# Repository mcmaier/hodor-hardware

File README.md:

# HODOR - Highly flexible Open-source Door Operation Regulator

## Overview

HODOR ("Holds your door") is a universal controller for sliding door motor systems. The device is designed to operate brushed DC motors ranging from 12 to 24V, providing a comprehensive control solution that can be configured via Wi-Fi for smart home integration.

The hardware design files were created in KiCAD 9.0.

## System Architecture

The HODOR system consists of four main subsystems:

1. **Controllerboard** - Central processing unit based on the ESP32-S3
2. **Power Supply** - Handles voltage regulation and power distribution
3. **Motor Control** - Manages motor drive with H-bridge driver and feedback systems
4. **Peripherals** - Provides additional I/O and integration capabilities

### Block Diagram

```
+---------------+    +----------------+
|    Power      |    |                |
|   Terminals   |----| Controllerboard|
|   12-24V      |    |   (ESP32-S3)   |<--->[SPI BUS]
+---------------+    |                |
                     |                |----+
                     +----------------+    |
                            ^              |
                            |              v
                            |        +----------------+
                            |        |  Peripherals   |
                            |        +----------------+
                            v
                     +----------------+
                     |  Motor Control |
                     |   H-Bridge     |
                     |   Encoder I/F  |
                     +----------------+
```

## Technical Specifications

| Input Voltage | Standby Current |
|---------------|-----------------|
| 12 V          | tbc             |
| 24 V          | tbc             |

## Subsystems

### Controller Board (ESP32-S3)

The central controller is based on an ESP32-S3 microcontroller that handles:
- Motor control with PWM outputs
- Safety monitoring
- Encoder feedback processing
- SPI communication with peripherals
- Wi-Fi connectivity for configuration and smart home integration

The controller connects to both the motor control subsystem and peripheral I/O expansion modules through a combination of digital signals and an SPI bus.

### Power Supply

The power subsystem converts the 12-24V input to the required voltages for the control circuits and provides:
- Input voltage sensing (`V_BUS_SENSE`)
- DC-link voltage monitoring (`V_DC_SENSE`)
- Protection circuitry

### Motor Control

The motor control subsystem features:
- H-bridge driver with PWM inputs (`DRV_PWM1`, `DRV_PWM2`)
- Driver enable control (`DRV_EN`)
- Fault monitoring (`DRV_~SF`)
- Safety trigger and clear mechanisms (`SAFETY_TRIG`, `SAFETY_~CLR`)
- Current sensing (`ADC_I_SENSE`, `ADC_DRV_FB`)
- Quadrature encoder interface (`ENCODER_A`, `ENCODER_B`)
- An independet brake chopper, that burns voltage peaks above 27 V, to protect the driver IC.

The H-bridge allows bidirectional control of the DC motor with variable speed control via PWM.

### Peripherals

The control device provides:
- Inputs (Potential free or 12..24 V DC)
- Status indicators
- Relay output

## Key Features

- Supports brushed DC motors from 12 to 24V
- H-bridge driver with current sensing for motor protection
- Quadrature encoder interface for precise position feedback
- Configurable inputs
- Programmable relay output
- Wi-Fi connectivity for configuration and smart home integration
- Safety mechanisms for door operation
- Open-source hardware and software design

## Applications

The HODOR controller is primarily designed for:
- Sliding door automation
- Other motor control applications with optional position feedback

## Project Status

This project is currently in development.

## Safety Features

HODOR incorporates several safety features:
- Current monitoring to detect obstructions
- Position feedback via quadrature encoder
- Hardware watchdog safety trigger 
- Fault detection in the motor driver

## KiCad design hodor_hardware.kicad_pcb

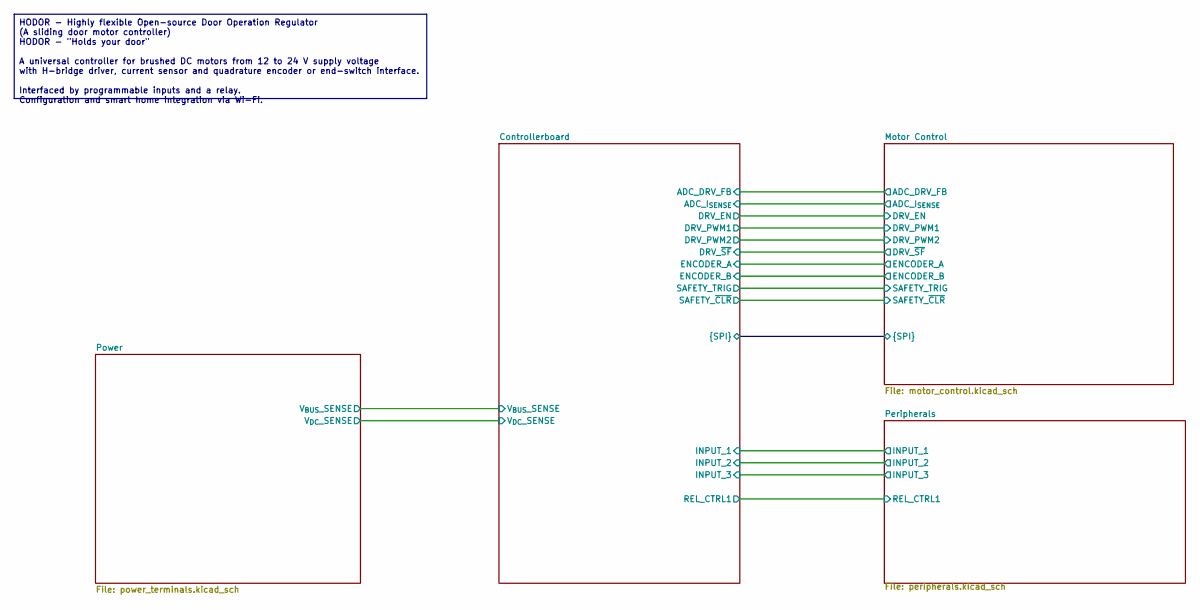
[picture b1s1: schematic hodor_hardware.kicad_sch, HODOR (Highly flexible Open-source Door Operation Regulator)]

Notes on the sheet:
HODOR - Highly flexible Open-source Door Operation Regulator (A sliding door motor controller) HODOR - "Holds your door" A universal controller for brushed DC motors from 12 to 24 V supply voltage with H-bridge driver, current sensor and quadrature encoder or end-switch interface. Interfaced by pro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

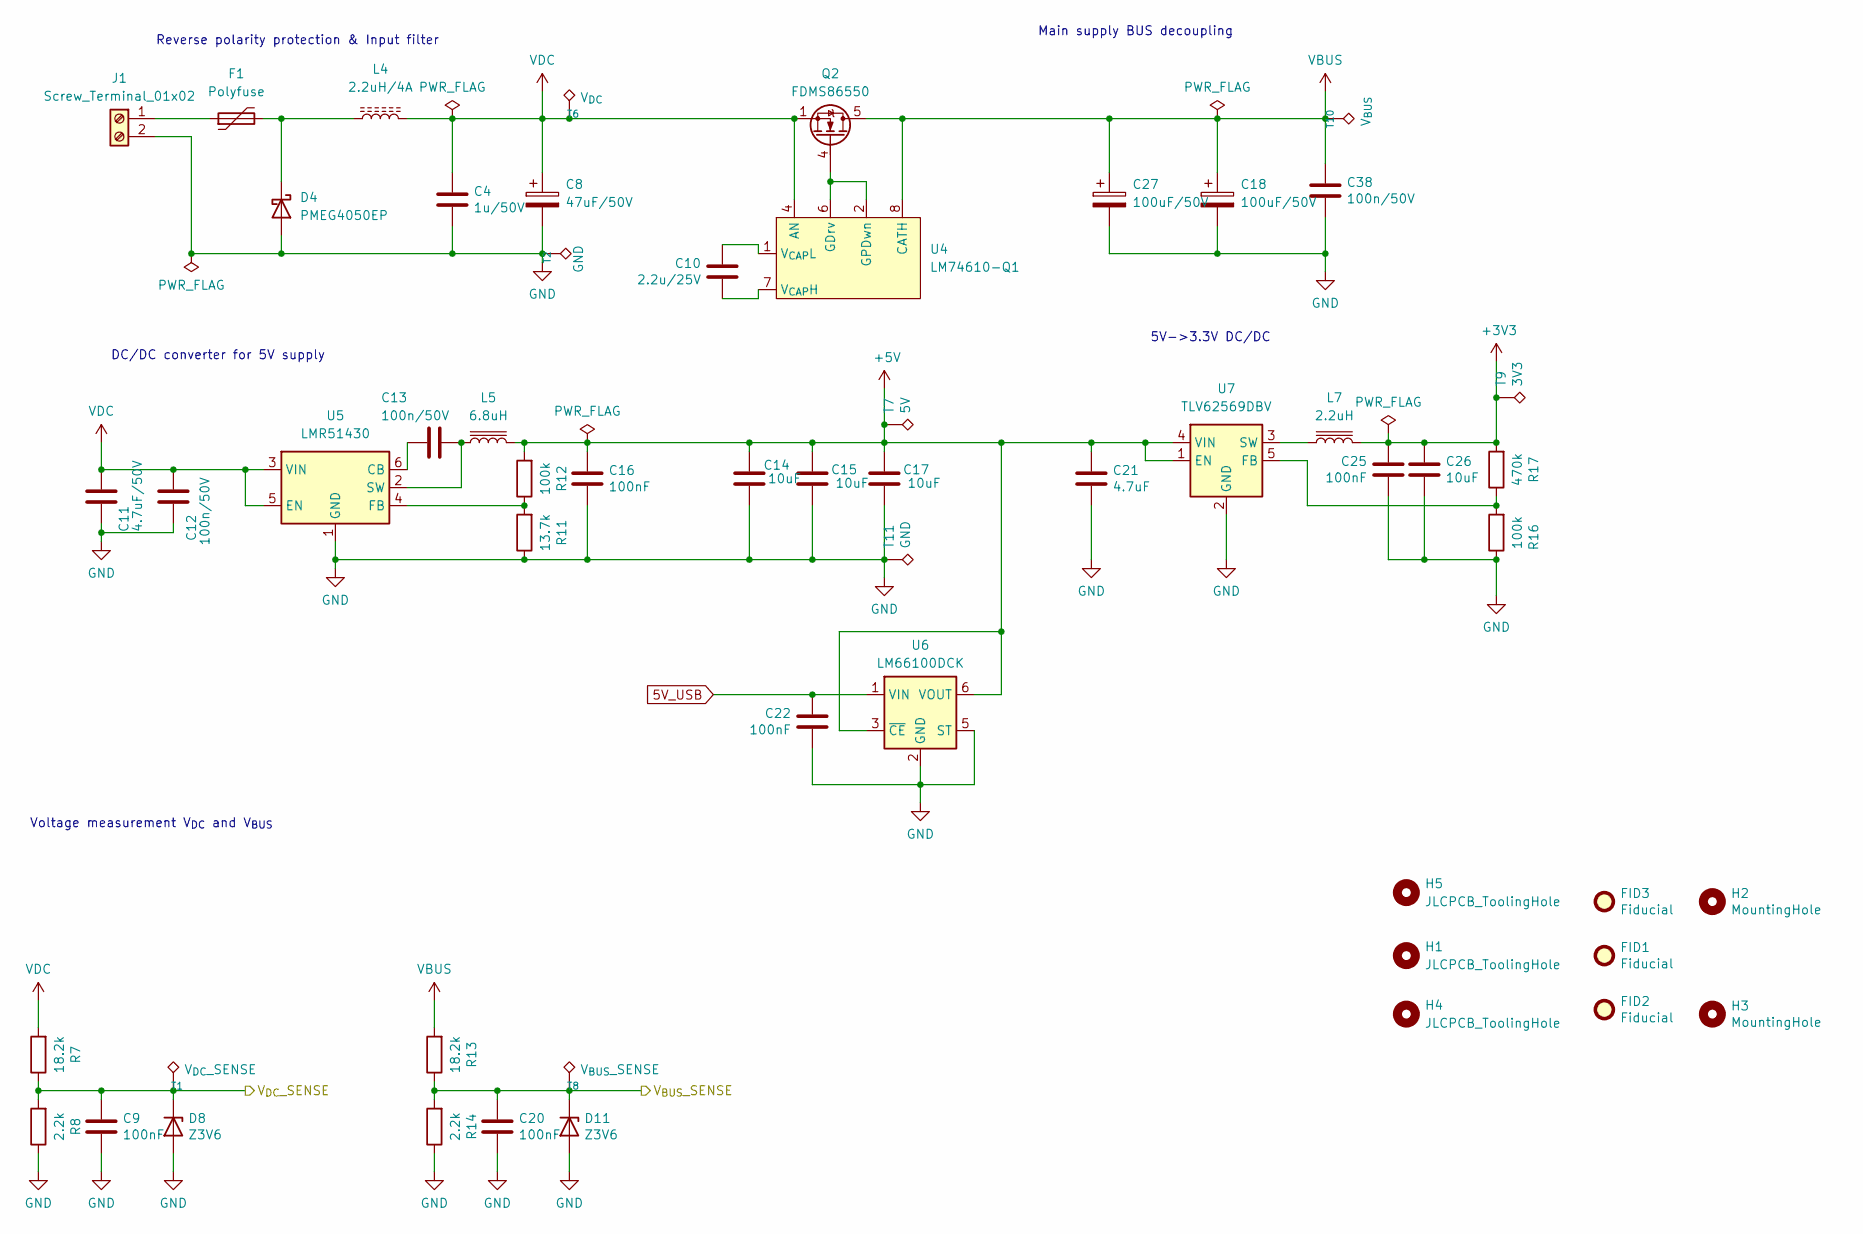
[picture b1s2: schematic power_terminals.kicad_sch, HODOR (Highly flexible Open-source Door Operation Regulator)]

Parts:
C4: 1u/50V; C_0805_2012Metric
C8: 47uF/50V; CP_Elec_6.3x5.8
C9, C16, C20, C22, C25: 100nF; C_0402_1005Metric
C10: 2.2u/25V; C_0805_2012Metric
C11: 4.7uF/50V; C_1206_3216Metric
C12, C13, C38: 100n/50V; C_0603_1608Metric
C14, C15, C17, C26: 10uF; C_0805_2012Metric
C18, C27: 100uF/50V; C_Elec_8x10.2
C21: 4.7uF; C_1206_3216Metric
D4: PMEG4050EP; D_SOD-128
D8, D11: Z3V6; D_SOD-523
F1: Polyfuse; Fuse_2920_7451Metric
FID1, FID2, FID3: Fiducial; Fiducial_1mm_Mask2mm
H1, H4, H5: JLCPCB_ToolingHole
H2, H3: MountingHole; MountingHole_3.2mm_M3
J1: Screw_Terminal_01x02; TerminalBlock_Phoenix_MKDS-1,5-2_1x02_P5.00mm_Horizontal
L4: 2.2uH/4A; L_Wuerth_MAPI-4020
L5: 6.8uH; L_Wuerth_WE-PD2-Typ-MS
L7: 2.2uH; L_1812_4532Metric
Q2: FDMS86550; TDSON-8-1
R7, R13: 18.2k; R_0402_1005Metric
R8, R14: 2.2k; R_0402_1005Metric
R11: 13.7k; R_0402_1005Metric
R12, R16: 100k; R_0402_1005Metric
R17: 470k; R_0402_1005Metric
T1: V_{DC}_SENSE; TestPoint_Pad_D1.0mm
T2, T11: GND; TestPoint_Pad_1.0x1.0mm
T6: V_{DC}; TestPoint_Pad_D1.0mm
T7: 5V; TestPoint_Pad_D1.0mm
T8: V_{BUS}_SENSE; TestPoint_Pad_D1.0mm
T9: 3V3; TestPoint_Pad_D1.0mm
T10: V_{BUS}; TestPoint_Pad_D1.0mm
U4: LM74610-Q1; VSSOP-8_3x3mm_P0.65mm
U5: LMR51430; SOT-23-6
U6: LM66100DCK; SOT-363_SC-70-6
U7: TLV62569DBV; SOT-23-5

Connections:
5V_USB: C22.2, U6.1 (VIN); also elsewhere on the board
+3V3: C25.1, C26.1, L7.2, R17.2, T9.1; also elsewhere on the board
+5V: C14.1, C15.1, C16.1, C17.1, C21.1, L5.2, R12.2, T7.1, U6.3 (~CE), U6.6 (VOUT), U7.1 (EN), U7.4 (VIN); also elsewhere on the board
/Controllerboard/V_{BUS}_SENSE: C20.1, D11.1 (K), R13.1, R14.2, T8.1; also elsewhere on the board
/Controllerboard/V_{DC}_SENSE: C9.1, D8.1 (K), R7.1, R8.2, T1.1; also elsewhere on the board
GND: C4.2, C8.2, C9.2, C11.2, C12.2, C14.2, C15.2, C16.2, C17.2, C18.2, C20.2, C21.2, C22.1, C25.2, C26.2, C27.2, C38.2, D4.2 (A), D8.2 (A), D11.2 (A), J1.2, R8.1, R11.1, R14.1, R16.1, T2.1, T11.1, U5.1 (GND), U6.2 (GND), U6.5 (ST), U7.2 (GND); also elsewhere on the board
unnamed: D4.1 (K), F1.2, L4.1
unnamed: F1.1, J1.1
unnamed: Q2.4 (G), U4.2 (GPDwn), U4.6 (GDrv)
unnamed: C10.2, U4.7 (V_{CAP}H)
unnamed: C10.1, U4.1 (V_{CAP}L)
unnamed: C13.2, U5.6 (CB)
unnamed: R11.2, R12.1, U5.4 (FB)
unnamed: C13.1, L5.1, U5.2 (SW)
unnamed: R16.2, R17.1, U7.5 (FB)
unnamed: L7.1, U7.3 (SW)
VBUS: C18.1, C27.1, C38.1, Q2.5 (D), R13.2, T10.1, U4.8 (CATH); also elsewhere on the board
VDC: C4.1, C8.1, C11.1, C12.1, L4.2, Q2.1 (S), Q2.2 (S), Q2.3 (S), R7.2, T6.1, U4.4 (AN), U5.3 (VIN), U5.5 (EN)

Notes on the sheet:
DC/DC converter for 5V supply
5V->3.3V DC/DC
Voltage measurement V_{DC} and V_{BUS}
Reverse polarity protection & Input filter
Main supply BUS decoupling

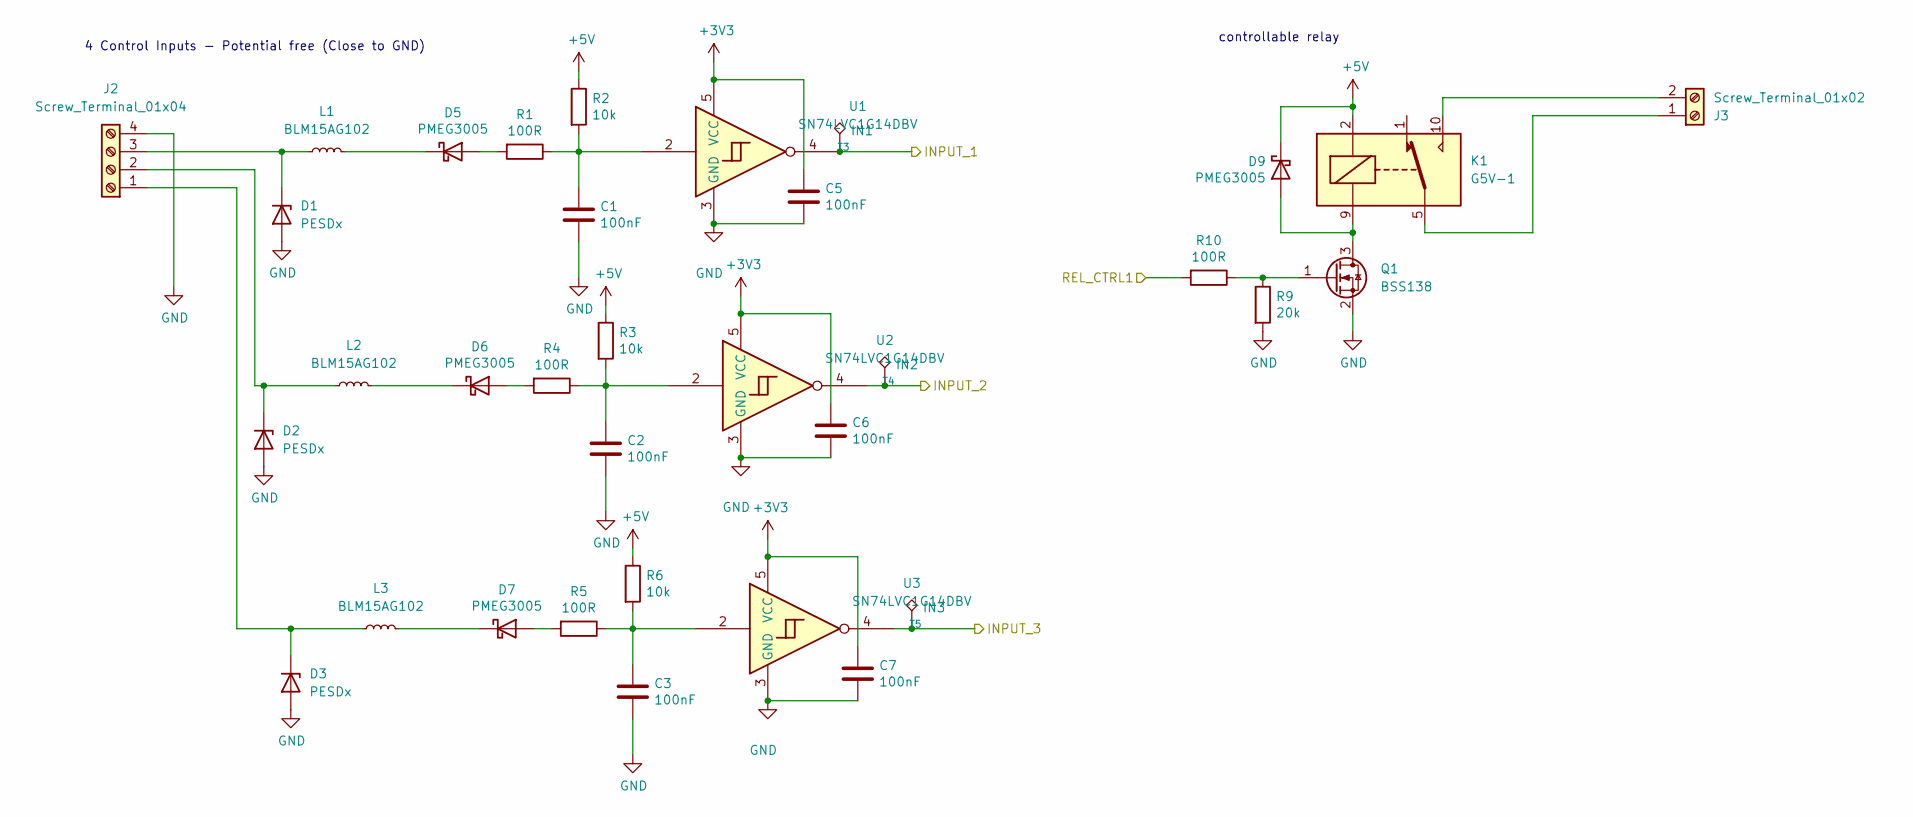
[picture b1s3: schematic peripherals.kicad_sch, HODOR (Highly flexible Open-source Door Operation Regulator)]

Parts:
C1, C2, C3, C5, C6, C7: 100nF; C_0402_1005Metric
D1, D2, D3: PESDx; D_SOD-523
D5, D6, D7, D9: PMEG3005; D_SOD-523
J2: Screw_Terminal_01x04; TerminalBlock_Phoenix_MKDS-1,5-4_1x04_P5.00mm_Horizontal
J3: Screw_Terminal_01x02; TerminalBlock_Phoenix_MKDS-1,5-2_1x02_P5.00mm_Horizontal
K1: G5V-1; Relay_SPDT_Omron_G5V-1
L1, L2, L3: BLM15AG102; L_0402_1005Metric
Q1: BSS138; SOT-23
R1, R4, R5, R10: 100R; R_0402_1005Metric
R2, R3, R6: 10k; R_0402_1005Metric
R9: 20k; R_0402_1005Metric
T3: IN1; TestPoint_Pad_D1.0mm
T4: IN2; TestPoint_Pad_D1.0mm
T5: IN3; TestPoint_Pad_D1.0mm
U1, U2, U3: SN74LVC1G14DBV; SOT-23-5

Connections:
+3V3: C5.1, C6.1, C7.1, U1.5 (VCC), U2.5 (VCC), U3.5 (VCC); also elsewhere on the board
+5V: D9.1 (K), K1.2, R2.1, R3.1, R6.1; also elsewhere on the board
/Controllerboard/INPUT_1: T3.1, U1.4; also elsewhere on the board
/Controllerboard/INPUT_2: T4.1, U2.4; also elsewhere on the board
/Controllerboard/INPUT_3: T5.1, U3.4; also elsewhere on the board
/Controllerboard/REL_CTRL1: R10.2; also elsewhere on the board
GND: C1.2, C2.2, C3.2, C5.2, C6.2, C7.2, D1.2 (A), D2.2 (A), D3.2 (A), J2.4, Q1.2 (S), R9.2, U1.3 (GND), U2.3 (GND), U3.3 (GND); also elsewhere on the board
unnamed: C1.1, R1.1, R2.2, U1.2
unnamed: C2.1, R3.2, R4.1, U2.2
unnamed: C3.1, R5.1, R6.2, U3.2
unnamed: D1.1 (K), J2.3, L1.1
unnamed: D2.1 (K), J2.2, L2.1
unnamed: D3.1 (K), J2.1, L3.1
unnamed: D5.2 (A), R1.2
unnamed: D5.1 (K), L1.2
unnamed: D6.2 (A), R4.2
unnamed: D6.1 (K), L2.2
unnamed: D7.2 (A), R5.2
unnamed: D7.1 (K), L3.2
unnamed: D9.2 (A), K1.9, Q1.3 (D)
unnamed: J3.1, K1.5, K1.6
unnamed: J3.2, K1.10
unnamed: Q1.1 (G), R9.1, R10.1

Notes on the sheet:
4 Control Inputs - Potential free (Close to GND)
controllable relay

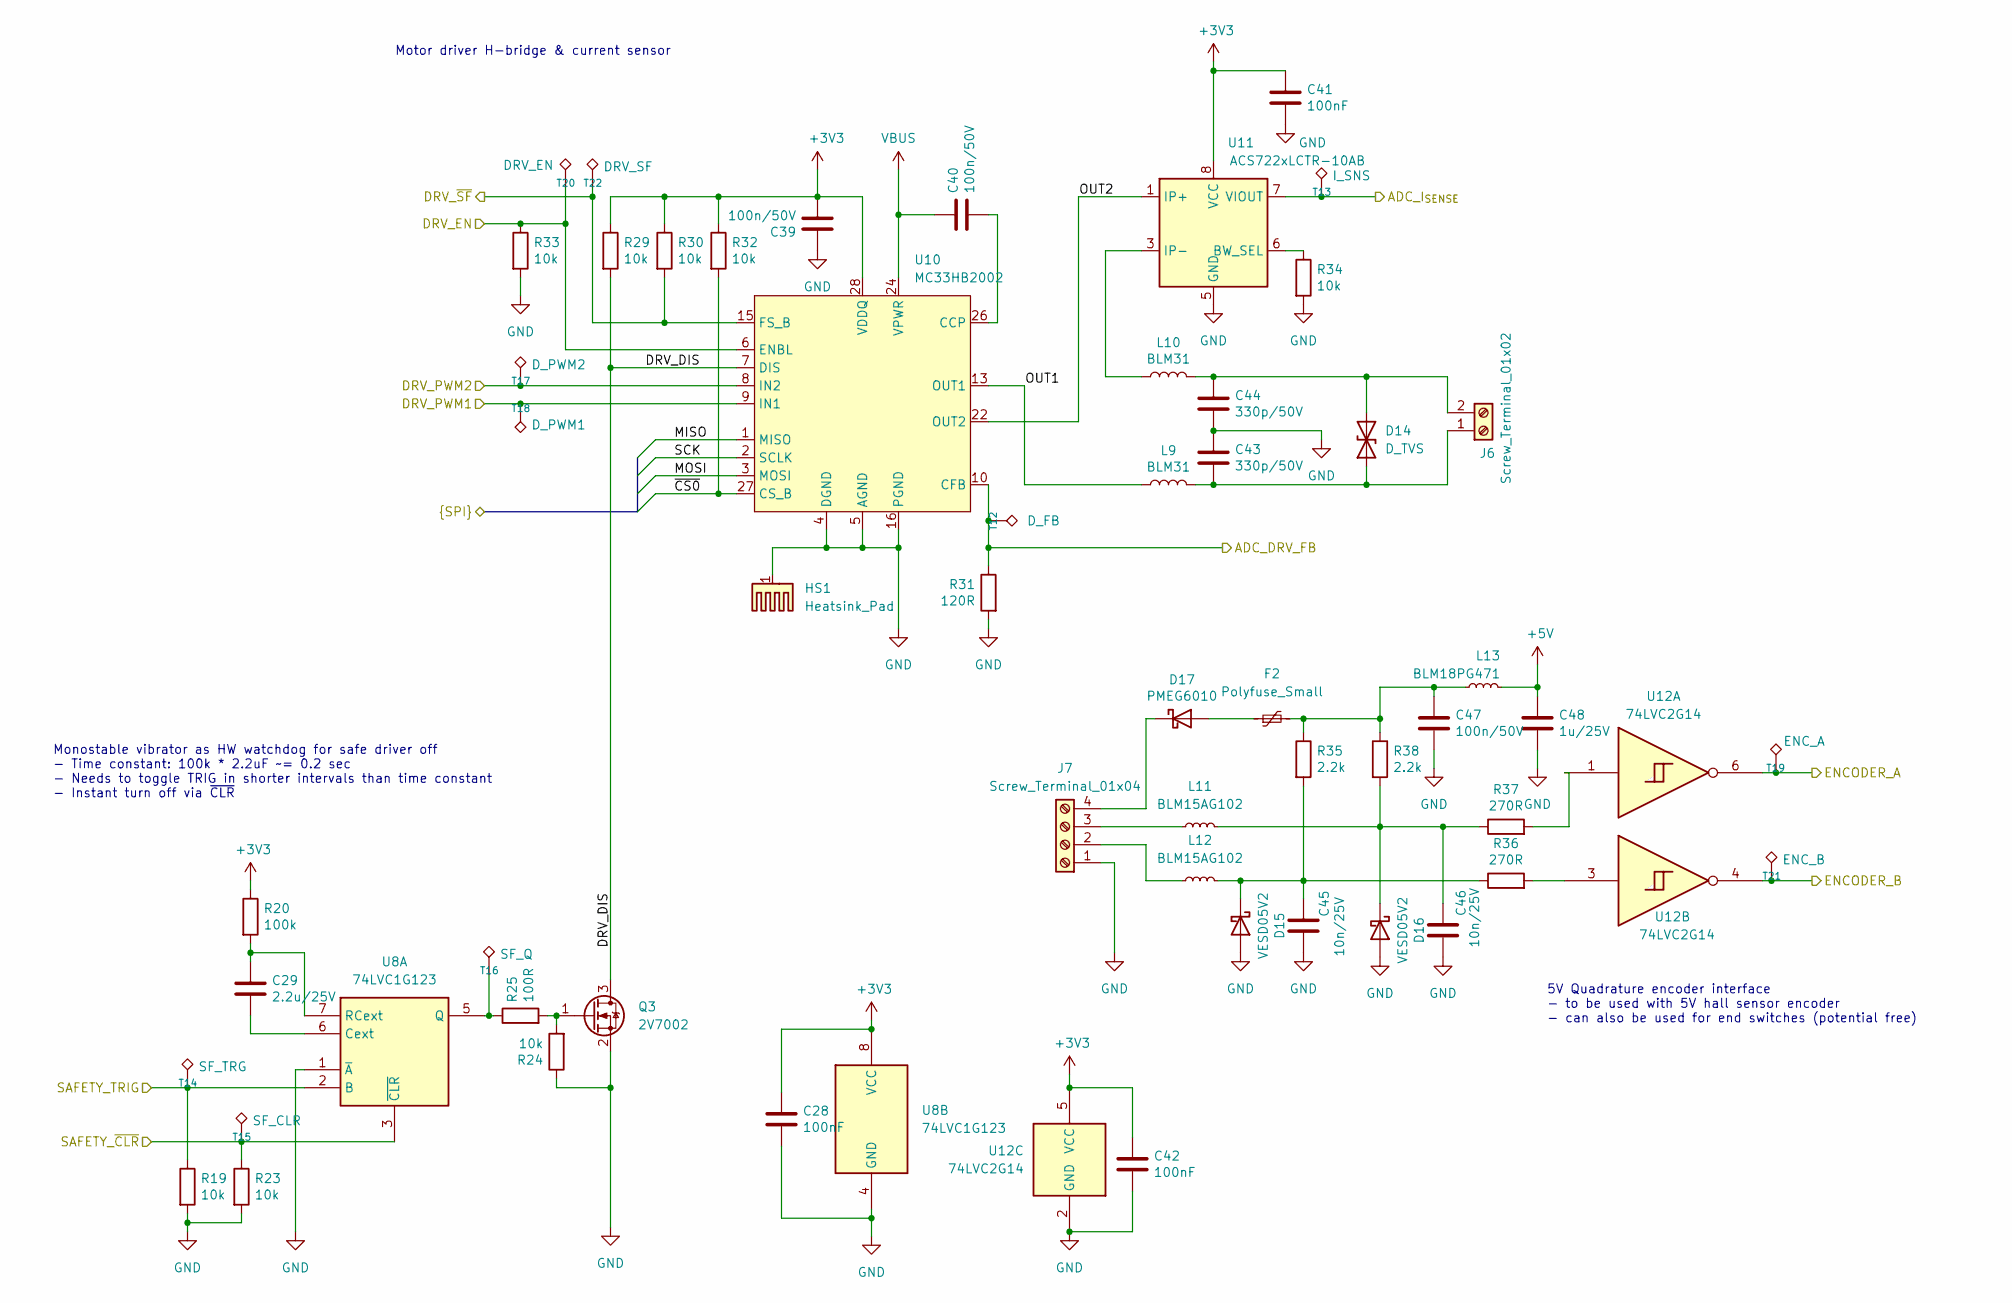
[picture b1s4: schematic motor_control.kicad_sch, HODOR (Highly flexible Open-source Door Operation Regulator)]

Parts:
C28, C41, C42: 100nF; C_0402_1005Metric
C29: 2.2u/25V; C_0805_2012Metric
C39, C40, C47: 100n/50V; C_0603_1608Metric
C43, C44: 330p/50V; C_0603_1608Metric
C45, C46: 10n/25V; C_0402_1005Metric
C48: 1u/25V; C_0603_1608Metric
D14: D_TVS; D_SMB
D15, D16: VESD05V2; D_SOD-523
D17: PMEG6010; D_SOD-123F
F2: Polyfuse_Small; Fuse_0805_2012Metric
HS1: Heatsink_Pad; Heatsink_AAVID_573300D00010G_TO-263
J6: Screw_Terminal_01x02; TerminalBlock_Phoenix_MKDS-1,5-2_1x02_P5.00mm_Horizontal
J7: Screw_Terminal_01x04; TerminalBlock_Phoenix_MKDS-1,5-4_1x04_P5.00mm_Horizontal
L9, L10: BLM31; L_1206_3216Metric
L11, L12: BLM15AG102; L_0402_1005Metric
L13: BLM18PG471; L_0603_1608Metric
Q3: 2V7002; SOT-323_SC-70
R19, R23, R24, R29, R30, R32, R33, R34: 10k; R_0402_1005Metric
R20: 100k; R_0402_1005Metric
R25: 100R; R_0402_1005Metric
R31: 120R; R_0603_1608Metric
R35, R38: 2.2k; R_0402_1005Metric
R36, R37: 270R; R_0402_1005Metric
T12: D_FB; TestPoint_Pad_D1.0mm
T13: I_SNS; TestPoint_Pad_D1.0mm
T14: SF_TRG; TestPoint_Pad_D1.0mm
T15: SF_CLR; TestPoint_Pad_D1.0mm
T16: SF_Q; TestPoint_Pad_D1.0mm
T17: D_PWM2; TestPoint_Pad_D1.0mm
T18: D_PWM1; TestPoint_Pad_D1.0mm
T19: ENC_A; TestPoint_Pad_D1.0mm
T20: DRV_EN; TestPoint_Pad_D1.0mm
T21: ENC_B; TestPoint_Pad_D1.0mm
T22: DRV_SF; TestPoint_Pad_D1.0mm
U8: 74LVC1G123; VSSOP-8_2.3x2mm_P0.5mm
U10: MC33HB2002; HVQFN-28-1EP_6x6mm_MC33HB2002
U11: ACS722xLCTR-10AB; SOIC-8_3.9x4.9mm_P1.27mm
U12: 74LVC2G14; SOT-23-6

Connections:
+3V3: C28.1, C39.2, C41.1, C42.1, R20.1, R29.1, R30.1, R32.1, U8.8 (VCC), U10.28 (VDDQ), U11.8 (VCC), U12.5 (VCC); also elsewhere on the board
+5V: C48.1, L13.2; also elsewhere on the board
/Controllerboard/ADC_DRV_FB: R31.1, T12.1, U10.10 (CFB); also elsewhere on the board
/Controllerboard/ADC_I_{SENSE}: T13.1, U11.7 (VIOUT); also elsewhere on the board
/Controllerboard/DRV_EN: R33.1, T20.1, U10.6 (ENBL); also elsewhere on the board
/Controllerboard/DRV_PWM1: T18.1, U10.9 (IN1); also elsewhere on the board
/Controllerboard/DRV_PWM2: T17.1, U10.8 (IN2); also elsewhere on the board
/Controllerboard/DRV_~SF: R30.2, T22.1, U10.15 (FS_B); also elsewhere on the board
/Controllerboard/ENCODER_A: T19.1, U12.6; also elsewhere on the board
/Controllerboard/ENCODER_B: T21.1, U12.4; also elsewhere on the board
/Controllerboard/MISO: U10.1 (MISO); also elsewhere on the board
/Controllerboard/MOSI: U10.3 (MOSI); also elsewhere on the board
/Controllerboard/SAFETY_TRIG: R19.1, T14.1, U8.2 (B); also elsewhere on the board
/Controllerboard/SAFETY_~CLR: R23.1, T15.1, U8.3 (~CLR); also elsewhere on the board
/Controllerboard/SCK: U10.2 (SCLK); also elsewhere on the board
/Controllerboard/~CS0: R32.2, U10.27 (CS_B); also elsewhere on the board
/Motor Control/DRV_DIS: Q3.3 (D), R29.2, U10.7 (DIS)
/Motor Control/OUT1: L9.1, U10.13 (OUT1), U10.14 (OUT1)
/Motor Control/OUT2: U10.22 (OUT2), U10.23 (OUT2), U11.1 (IP+), U11.2 (IP+)
GND: C28.2, C39.1, C41.2, C42.2, C43.1, C44.2, C45.2, C46.2, C47.2, C48.2, D15.2 (A), D16.2 (A), HS1.1, J7.1, Q3.2 (S), R19.2, R23.2, R24.1, R31.2, R33.2, R34.2, U8.1 (~A), U8.4 (GND), U10.4 (DGND), U10.5 (AGND), U10.16 (PGND), U10.17 (PGND), U10.18 (PGND), U10.19 (PGND), U10.20 (PGND), U10.21 (AGND), U10.29 (AGND), U11.5 (GND), U12.2 (GND); also elsewhere on the board
unnamed: C47.1, F2.2, L13.1, R35.1, R38.1
unnamed: C43.2, D14.1 (A1), J6.1, L9.2
unnamed: C44.1, D14.2 (A2), J6.2, L10.2
unnamed: C45.1, D15.1 (K), L12.2, R35.2, R36.1
unnamed: C46.1, D16.1 (K), L11.2, R37.1, R38.2
unnamed: D17.2 (A), F2.1
unnamed: D17.1 (K), J7.4
unnamed: J7.2, L12.1
unnamed: J7.3, L11.1
unnamed: L10.1, U11.3 (IP-), U11.4 (IP-)
unnamed: Q3.1 (G), R24.2, R25.2
unnamed: R36.2, U12.3
unnamed: R37.2, U12.1
unnamed: C29.2, U8.6 (Cext)
unnamed: R25.1, T16.1, U8.5 (Q)
unnamed: C29.1, R20.2, U8.7 (RCext)
unnamed: C40.2, U10.26 (CCP)
unnamed: R34.1, U11.6 (BW_SEL)
VBUS: C40.1, U10.11 (VPWR), U10.12 (VPWR), U10.24 (VPWR), U10.25 (VPWR); also elsewhere on the board

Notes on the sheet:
5V Quadrature encoder interface - to be used with 5V hall sensor encoder - can also be used for end switches (potential free)
Motor driver H-bridge & current sensor
Monostable vibrator as HW watchdog for safe driver off - Time constant: 100k * 2.2uF ~= 0.2 sec - Needs to toggle TRIG in shorter intervals than time constant - Instant turn off via ~{CLR}

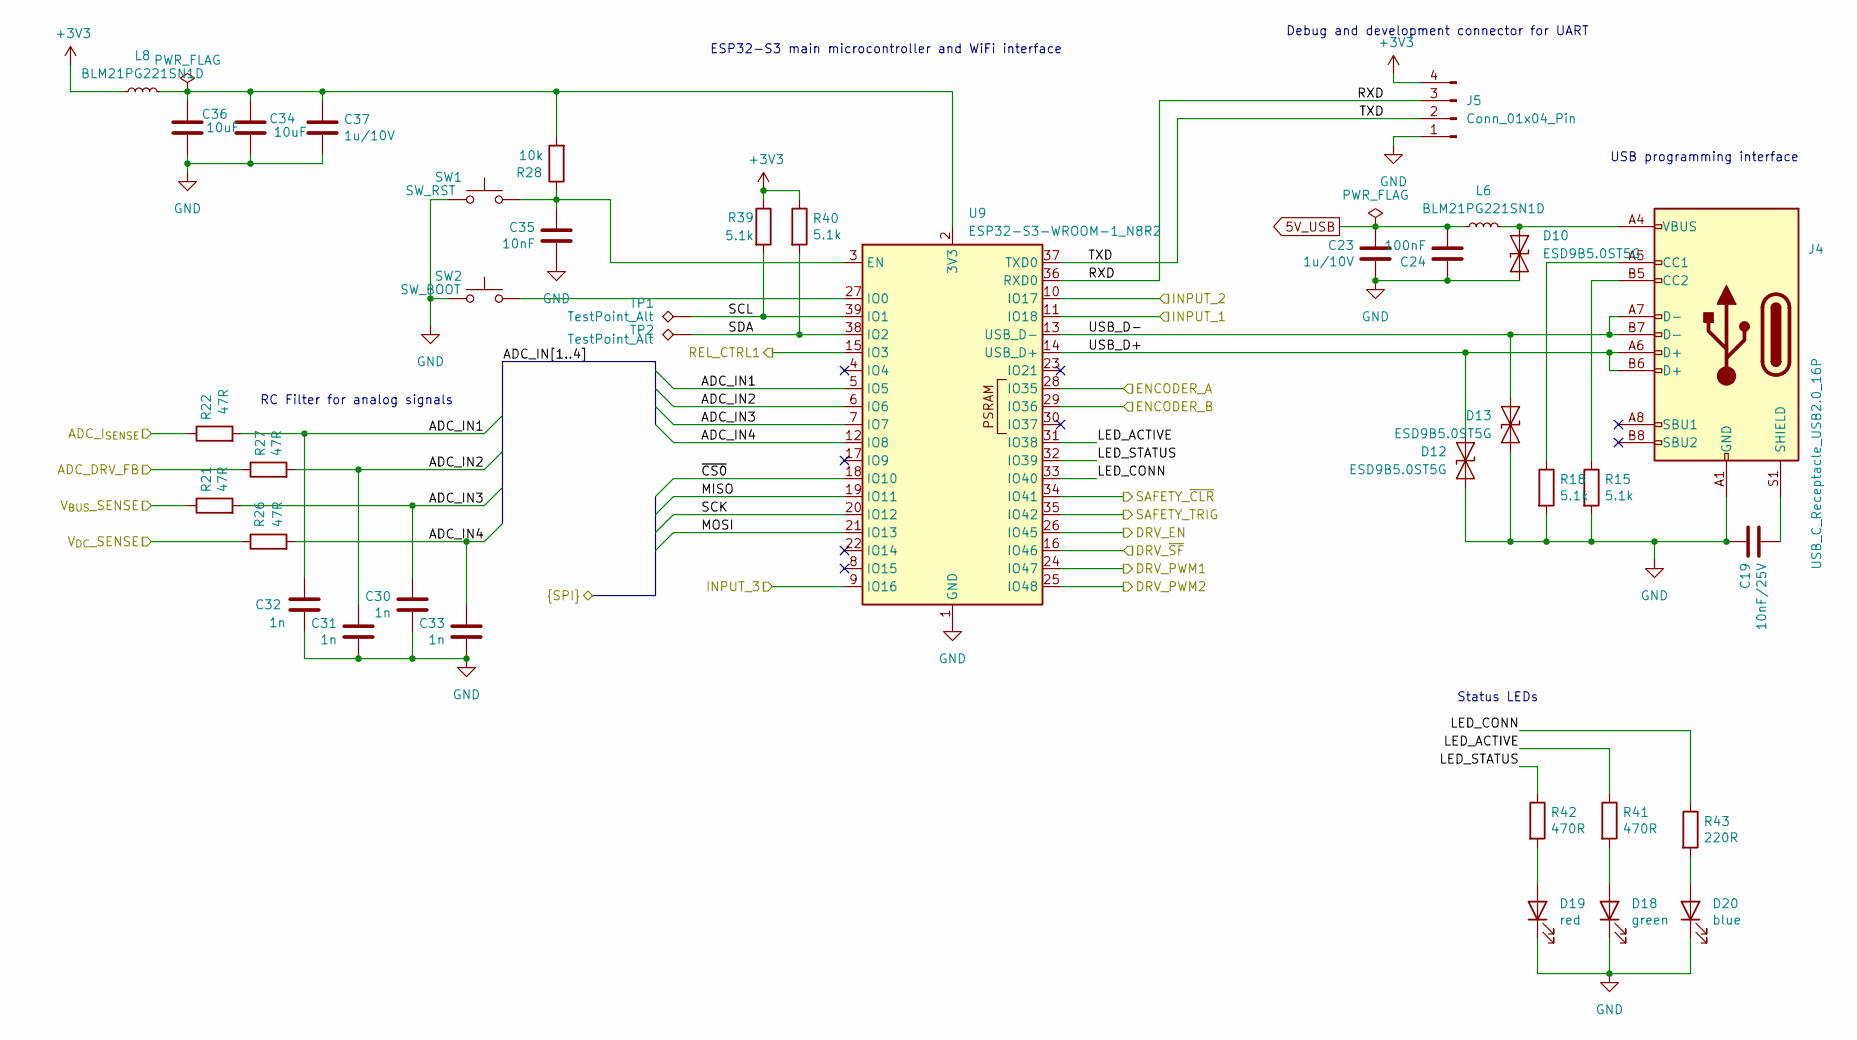
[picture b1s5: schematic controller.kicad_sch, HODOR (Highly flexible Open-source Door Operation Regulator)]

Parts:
C19: 10nF/25V; C_0402_1005Metric
C23, C37: 1u/10V; C_0402_1005Metric
C24: 100nF; C_0402_1005Metric
C30, C31, C32, C33: 1n; C_0402_1005Metric
C34, C36: 10uF; C_0805_2012Metric
C35: 10nF; C_0402_1005Metric
D10, D12, D13: ESD9B5.0ST5G; D_SOD-923
D18: green; LED_0603_1608Metric
D19: red; LED_0603_1608Metric
D20: blue; LED_0603_1608Metric
J4: USB_C_Receptacle_USB2.0_16P; USB_C_Receptacle_G-Switch_GT-USB-7010ASV
J5: Conn_01x04_Pin; PinHeader_1x04_P2.54mm_Vertical
L6, L8: BLM21PG221SN1D; L_0805_2012Metric
R15, R18, R39, R40: 5.1k; R_0402_1005Metric
R21, R22, R26, R27: 47R; R_0402_1005Metric
R28: 10k; R_0402_1005Metric
R41, R42: 470R; R_0402_1005Metric
R43: 220R; R_0402_1005Metric
SW1: SW_RST; SW_Push_SPST_NO_Alps_SKRK
SW2: SW_BOOT; SW_Push_SPST_NO_Alps_SKRK
TP1, TP2: TestPoint_Alt; TestPoint_Pad_1.0x1.0mm
U9: ESP32-S3-WROOM-1_N8R2; ESP32-S3-WROOM-1U

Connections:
5V_USB: C23.2, C24.1, L6.1; also elsewhere on the board
+3V3: J5.4, L8.1, R39.1, R40.1; also elsewhere on the board
/Controllerboard/ADC_DRV_FB: R27.1; also elsewhere on the board
/Controllerboard/ADC_IN1: C32.2, R22.2, U9.5 (IO5)
/Controllerboard/ADC_IN2: C31.2, R27.2, U9.6 (IO6)
/Controllerboard/ADC_IN3: C30.2, R21.2, U9.7 (IO7)
/Controllerboard/ADC_IN4: C33.2, R26.2, U9.12 (IO8)
/Controllerboard/ADC_I_{SENSE}: R22.1; also elsewhere on the board
/Controllerboard/DRV_EN: U9.26 (IO45); also elsewhere on the board
/Controllerboard/DRV_PWM1: U9.24 (IO47); also elsewhere on the board
/Controllerboard/DRV_PWM2: U9.25 (IO48); also elsewhere on the board
/Controllerboard/DRV_~SF: U9.16 (IO46); also elsewhere on the board
/Controllerboard/ENCODER_A: U9.28 (IO35); also elsewhere on the board
/Controllerboard/ENCODER_B: U9.29 (IO36); also elsewhere on the board
/Controllerboard/INPUT_1: U9.11 (IO18); also elsewhere on the board
/Controllerboard/INPUT_2: U9.10 (IO17); also elsewhere on the board
/Controllerboard/INPUT_3: U9.9 (IO16); also elsewhere on the board
/Controllerboard/LED_ACTIVE: R41.1, U9.31 (IO38)
/Controllerboard/LED_CONN: R43.1, U9.33 (IO40)
/Controllerboard/LED_STATUS: R42.1, U9.32 (IO39)
/Controllerboard/MISO: U9.19 (IO11); also elsewhere on the board
/Controllerboard/MOSI: U9.21 (IO13); also elsewhere on the board
/Controllerboard/REL_CTRL1: U9.15 (IO3); also elsewhere on the board
/Controllerboard/RXD: J5.3, U9.36 (RXD0)
/Controllerboard/SAFETY_TRIG: U9.35 (IO42); also elsewhere on the board
/Controllerboard/SAFETY_~CLR: U9.34 (IO41); also elsewhere on the board
/Controllerboard/SCK: U9.20 (IO12); also elsewhere on the board
/Controllerboard/SCL: R39.2, TP1.1, U9.39 (IO1)
/Controllerboard/SDA: R40.2, TP2.1, U9.38 (IO2)
/Controllerboard/TXD: J5.2, U9.37 (TXD0)
/Controllerboard/USB_D+: D12.2 (A2), J4.A6 (D+), J4.B6 (D+), U9.14 (USB_D+)
/Controllerboard/USB_D-: D13.2 (A2), J4.A7 (D-), J4.B7 (D-), U9.13 (USB_D-)
/Controllerboard/V_{BUS}_SENSE: R21.1; also elsewhere on the board
/Controllerboard/V_{DC}_SENSE: R26.1; also elsewhere on the board
/Controllerboard/~CS0: U9.18 (IO10); also elsewhere on the board
GND: C19.2, C23.1, C24.2, C30.1, C31.1, C32.1, C33.1, C34.2, C35.1, C36.2, C37.1, D10.1 (A1), D12.1 (A1), D13.1 (A1), D18.1 (K), D19.1 (K), D20.1 (K), J4.A1 (GND), J4.A12 (GND), J4.B1 (GND), J4.B12 (GND), J5.1, R15.2, R18.2, SW1.1, SW2.1, U9.1 (GND), U9.40 (GND), U9.41 (GND); also elsewhere on the board
unnamed: D10.2 (A2), J4.A4 (VBUS), J4.A9 (VBUS), J4.B4 (VBUS), J4.B9 (VBUS), L6.2
unnamed: D18.2 (A), R41.2
unnamed: D19.2 (A), R42.2
unnamed: D20.2 (A), R43.2
unnamed: J4.A5 (CC1), R18.1
unnamed: J4.B5 (CC2), R15.1
unnamed: C19.1, J4.S1 (SHIELD)
unnamed: C34.1, C36.1, C37.2, L8.2, R28.2, U9.2 (3V3)
unnamed: C35.2, R28.1, SW1.2, U9.3 (EN)
unnamed: SW2.2, U9.27 (IO0)

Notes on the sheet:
Status LEDs
RC Filter for analog signals
Debug and development connector for UART
ESP32-S3 main microcontroller and WiFi interface
USB programming interface

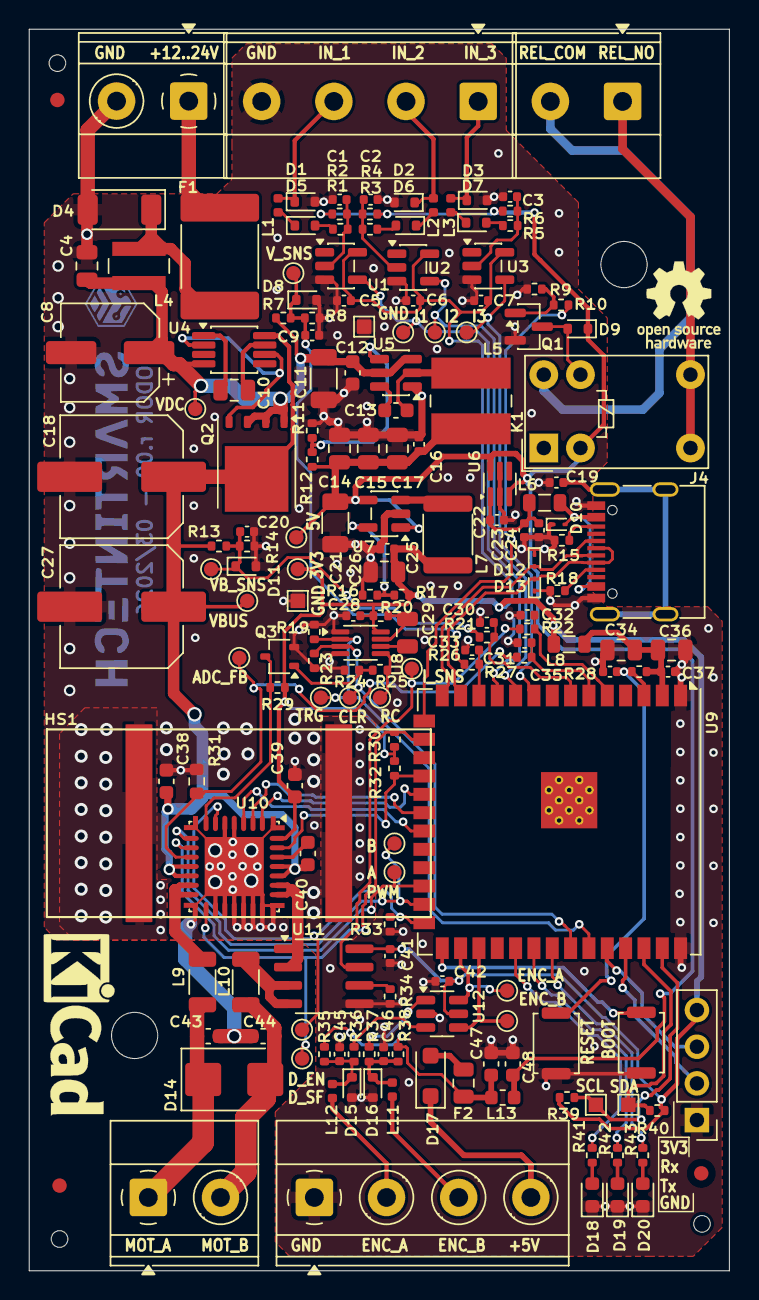
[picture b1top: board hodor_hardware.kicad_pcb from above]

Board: 2 copper layers, 48.5 x 86.0 mm, 184 parts (0 on the bottom side), 96 nets.

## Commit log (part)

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2026-03-25 Initial commit: HODOR hardware design files (KiCad 9)
2026-03-25 Simplified design (Old version switched to hodor-max)
2026-03-27 All nets connected
2026-03-27 Finalized Layout
